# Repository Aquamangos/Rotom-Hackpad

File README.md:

# Why?
Quick side project for [Hackclub](https://hackclub.com/) -> [Stardance](https://stardance.hackclub.com) -> [Hackpad Program](https://hackpad.hackclub.com/)

Also rotom seemed cool yk

# Keyboard Rotom
A 3x3 matrix mini keyboard reassembling a Phone Rotom from the popular series「Pokémon」

Main personal usage would be for volume control and macro keys (mic mute, etc)

# Main features
+ 9 programable buttons for macros/keys
+ 1 Rotary encoder knob for volume control
+ 1 OLED display for art/animations (In my case its his mouth)
+ 9 LEDs for cool effects (RBG yay)

# Finished Product
[Rotom Showcase](https://youtube.com/shorts/KLTXd5W2Blc)

# CAD models
Full models / simple case designs with Fusion 360.
The Pokéball is the knob attachment in this design

# PCB Model
The amount of silkscreen MIGHT be a little overkill...

# PCB Schematics
First time using KiCad!

# Bill of Materials

+ 1x PCB from JCLPCB
+ 3x 3D printed parts [Top|Bottom|Knob Attachment]
+ 9x through-hole 1N4148 Diodes
+ 9x MX-Style switches
+ 1x EC11 Rotary encoders
+ 1x 0.91 inch OLED display 
+ 9x white blank DSA keycaps
+ 9x SK6812 MINI-E LEDs
+ 4x M3x16mm screws
+ 4x M3x5mx4mm heatset inserts

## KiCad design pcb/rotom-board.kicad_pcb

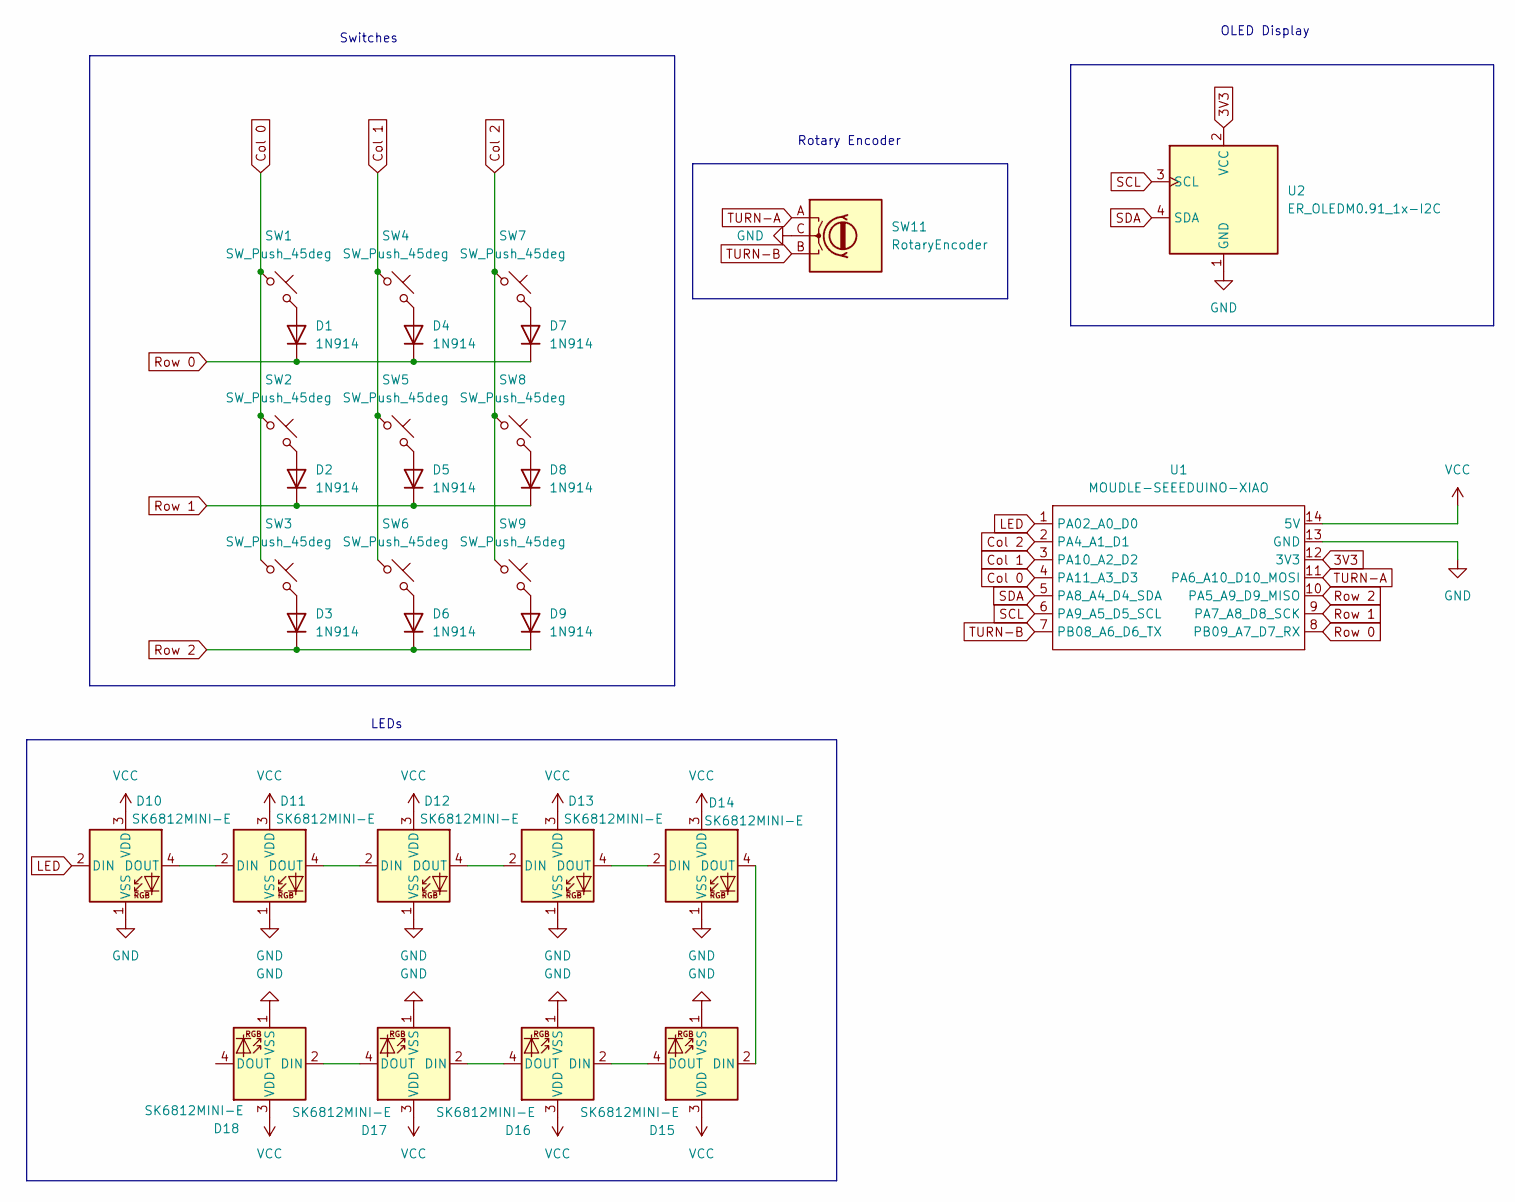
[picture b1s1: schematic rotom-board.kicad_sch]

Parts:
D1, D2, D3, D4, D5, D6, D7, D8, D9: 1N914; D_DO-35_SOD27_P7.62mm_Horizontal
D10, D11, D12, D13, D14, D15, D16, D17, D18: SK6812MINI-E; SK6812MINI-E_fixed
SW1, SW2, SW3, SW4, SW5, SW6, SW7, SW8, SW9: SW_Push_45deg; SW_Cherry_MX_1.00u_PCB
SW11: RotaryEncoder; RotaryEncoder_Alps_EC11E_Vertical_H20mm
U1: MOUDLE-SEEEDUINO-XIAO; XIAO-Generic-Hybrid-14P-2.54-21X17.8MM
U2: ER_OLEDM0.91_1x-I2C

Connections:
3V3: U1.12 (3V3), U2.2 (VCC)
Col 0: SW1.1, SW2.1, SW3.1, U1.4 (PA11_A3_D3)
Col 1: SW4.1, SW5.1, SW6.1, U1.3 (PA10_A2_D2)
Col 2: SW7.1, SW8.1, SW9.1, U1.2 (PA4_A1_D1)
GND: D10.1 (VSS), D11.1 (VSS), D12.1 (VSS), D13.1 (VSS), D14.1 (VSS), D15.1 (VSS), D16.1 (VSS), D17.1 (VSS), D18.1 (VSS), SW11.C, U1.13 (GND), U2.1 (GND)
LED: D10.2 (DIN), U1.1 (PA02_A0_D0)
unnamed: D1.2 (A), SW1.2
unnamed: D2.2 (A), SW2.2
unnamed: D3.2 (A), SW3.2
unnamed: D4.2 (A), SW4.2
unnamed: D5.2 (A), SW5.2
unnamed: D6.2 (A), SW6.2
unnamed: D7.2 (A), SW7.2
unnamed: D8.2 (A), SW8.2
unnamed: D9.2 (A), SW9.2
unnamed: D10.4 (DOUT), D11.2 (DIN)
unnamed: D11.4 (DOUT), D12.2 (DIN)
unnamed: D12.4 (DOUT), D13.2 (DIN)
unnamed: D13.4 (DOUT), D14.2 (DIN)
unnamed: D14.4 (DOUT), D15.2 (DIN)
unnamed: D15.4 (DOUT), D16.2 (DIN)
unnamed: D16.4 (DOUT), D17.2 (DIN)
unnamed: D17.4 (DOUT), D18.2 (DIN)
Row 0: D1.1 (K), D4.1 (K), D7.1 (K), U1.8 (PB09_A7_D7_RX)
Row 1: D2.1 (K), D5.1 (K), D8.1 (K), U1.9 (PA7_A8_D8_SCK)
Row 2: D3.1 (K), D6.1 (K), D9.1 (K), U1.10 (PA5_A9_D9_MISO)
SCL: U1.6 (PA9_A5_D5_SCL), U2.3 (SCL)
SDA: U1.5 (PA8_A4_D4_SDA), U2.4 (SDA)
TURN-A: SW11.A, U1.11 (PA6_A10_D10_MOSI)
TURN-B: SW11.B, U1.7 (PB08_A6_D6_TX)
VCC: D10.3 (VDD), D11.3 (VDD), D12.3 (VDD), D13.3 (VDD), D14.3 (VDD), D15.3 (VDD), D16.3 (VDD), D17.3 (VDD), D18.3 (VDD), U1.14 (5V)

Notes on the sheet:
Switches
LEDs
OLED Display
Rotary Encoder

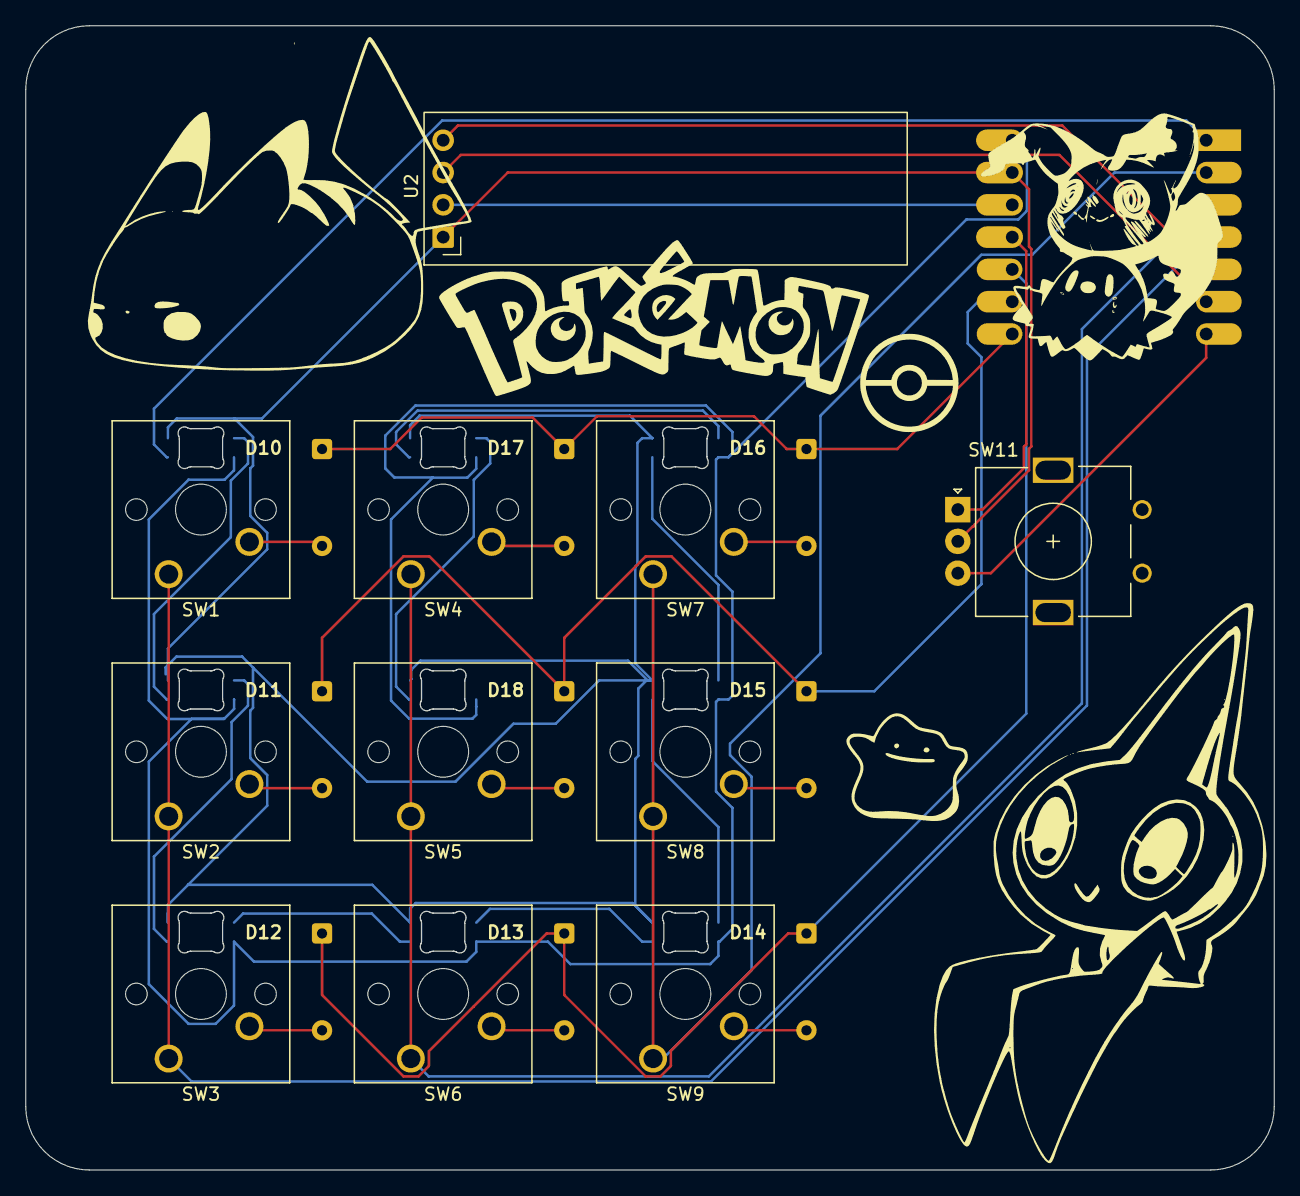
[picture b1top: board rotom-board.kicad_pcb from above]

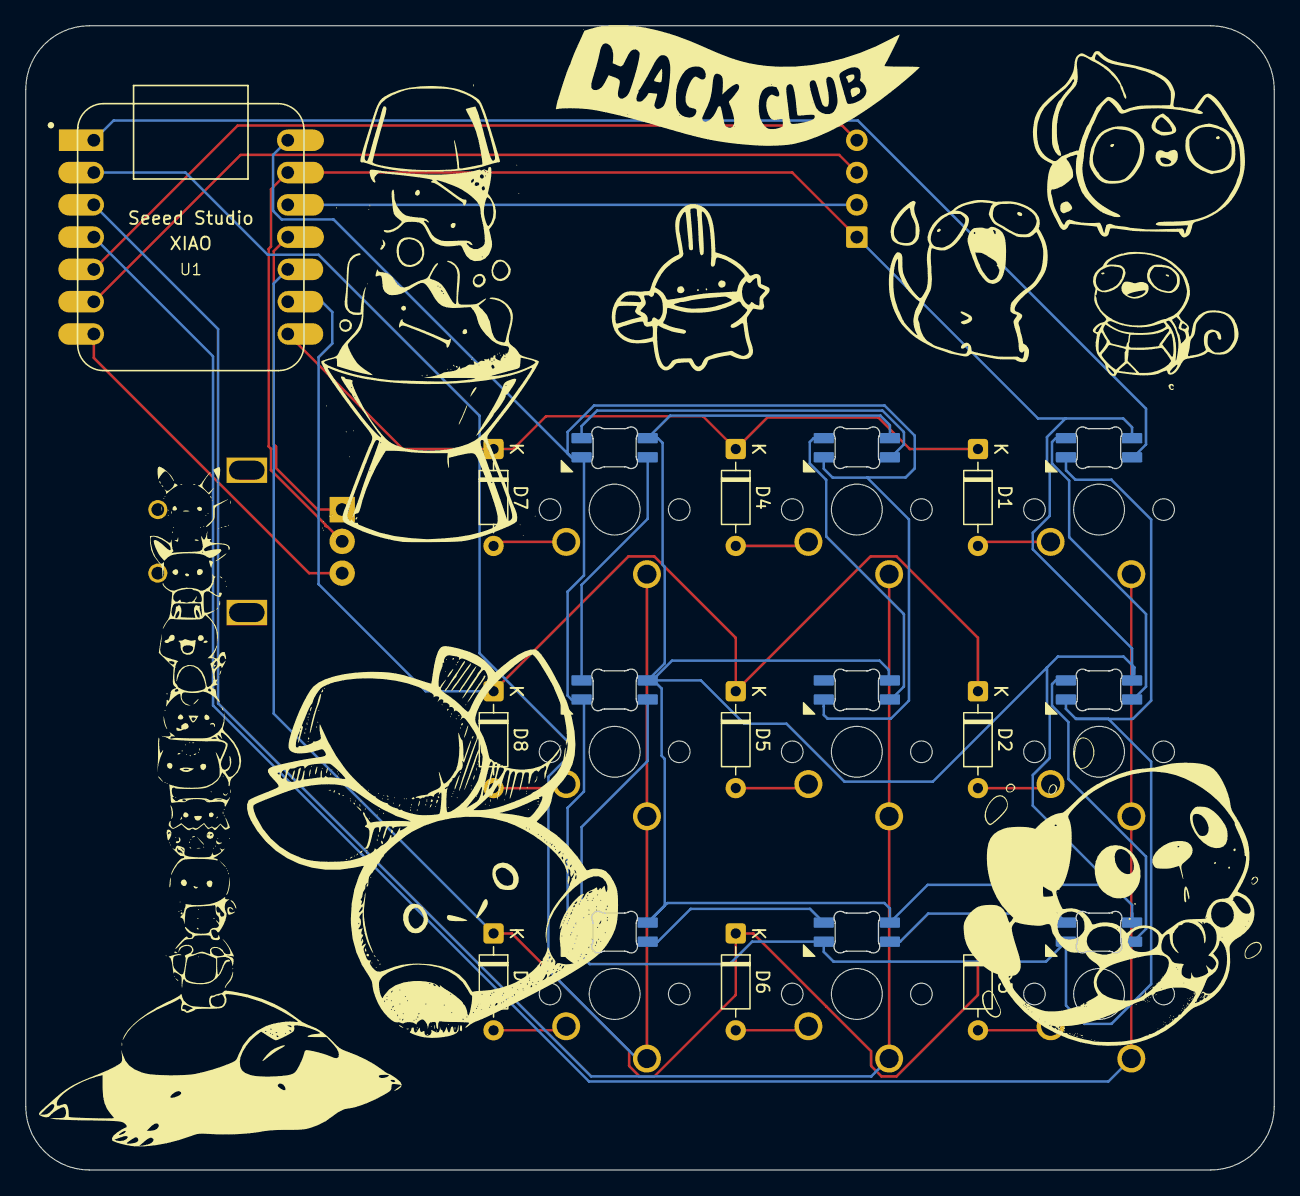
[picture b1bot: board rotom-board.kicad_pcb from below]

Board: 2 copper layers, 98.2 x 90.0 mm, 30 parts (10 on the bottom side), 31 nets.
